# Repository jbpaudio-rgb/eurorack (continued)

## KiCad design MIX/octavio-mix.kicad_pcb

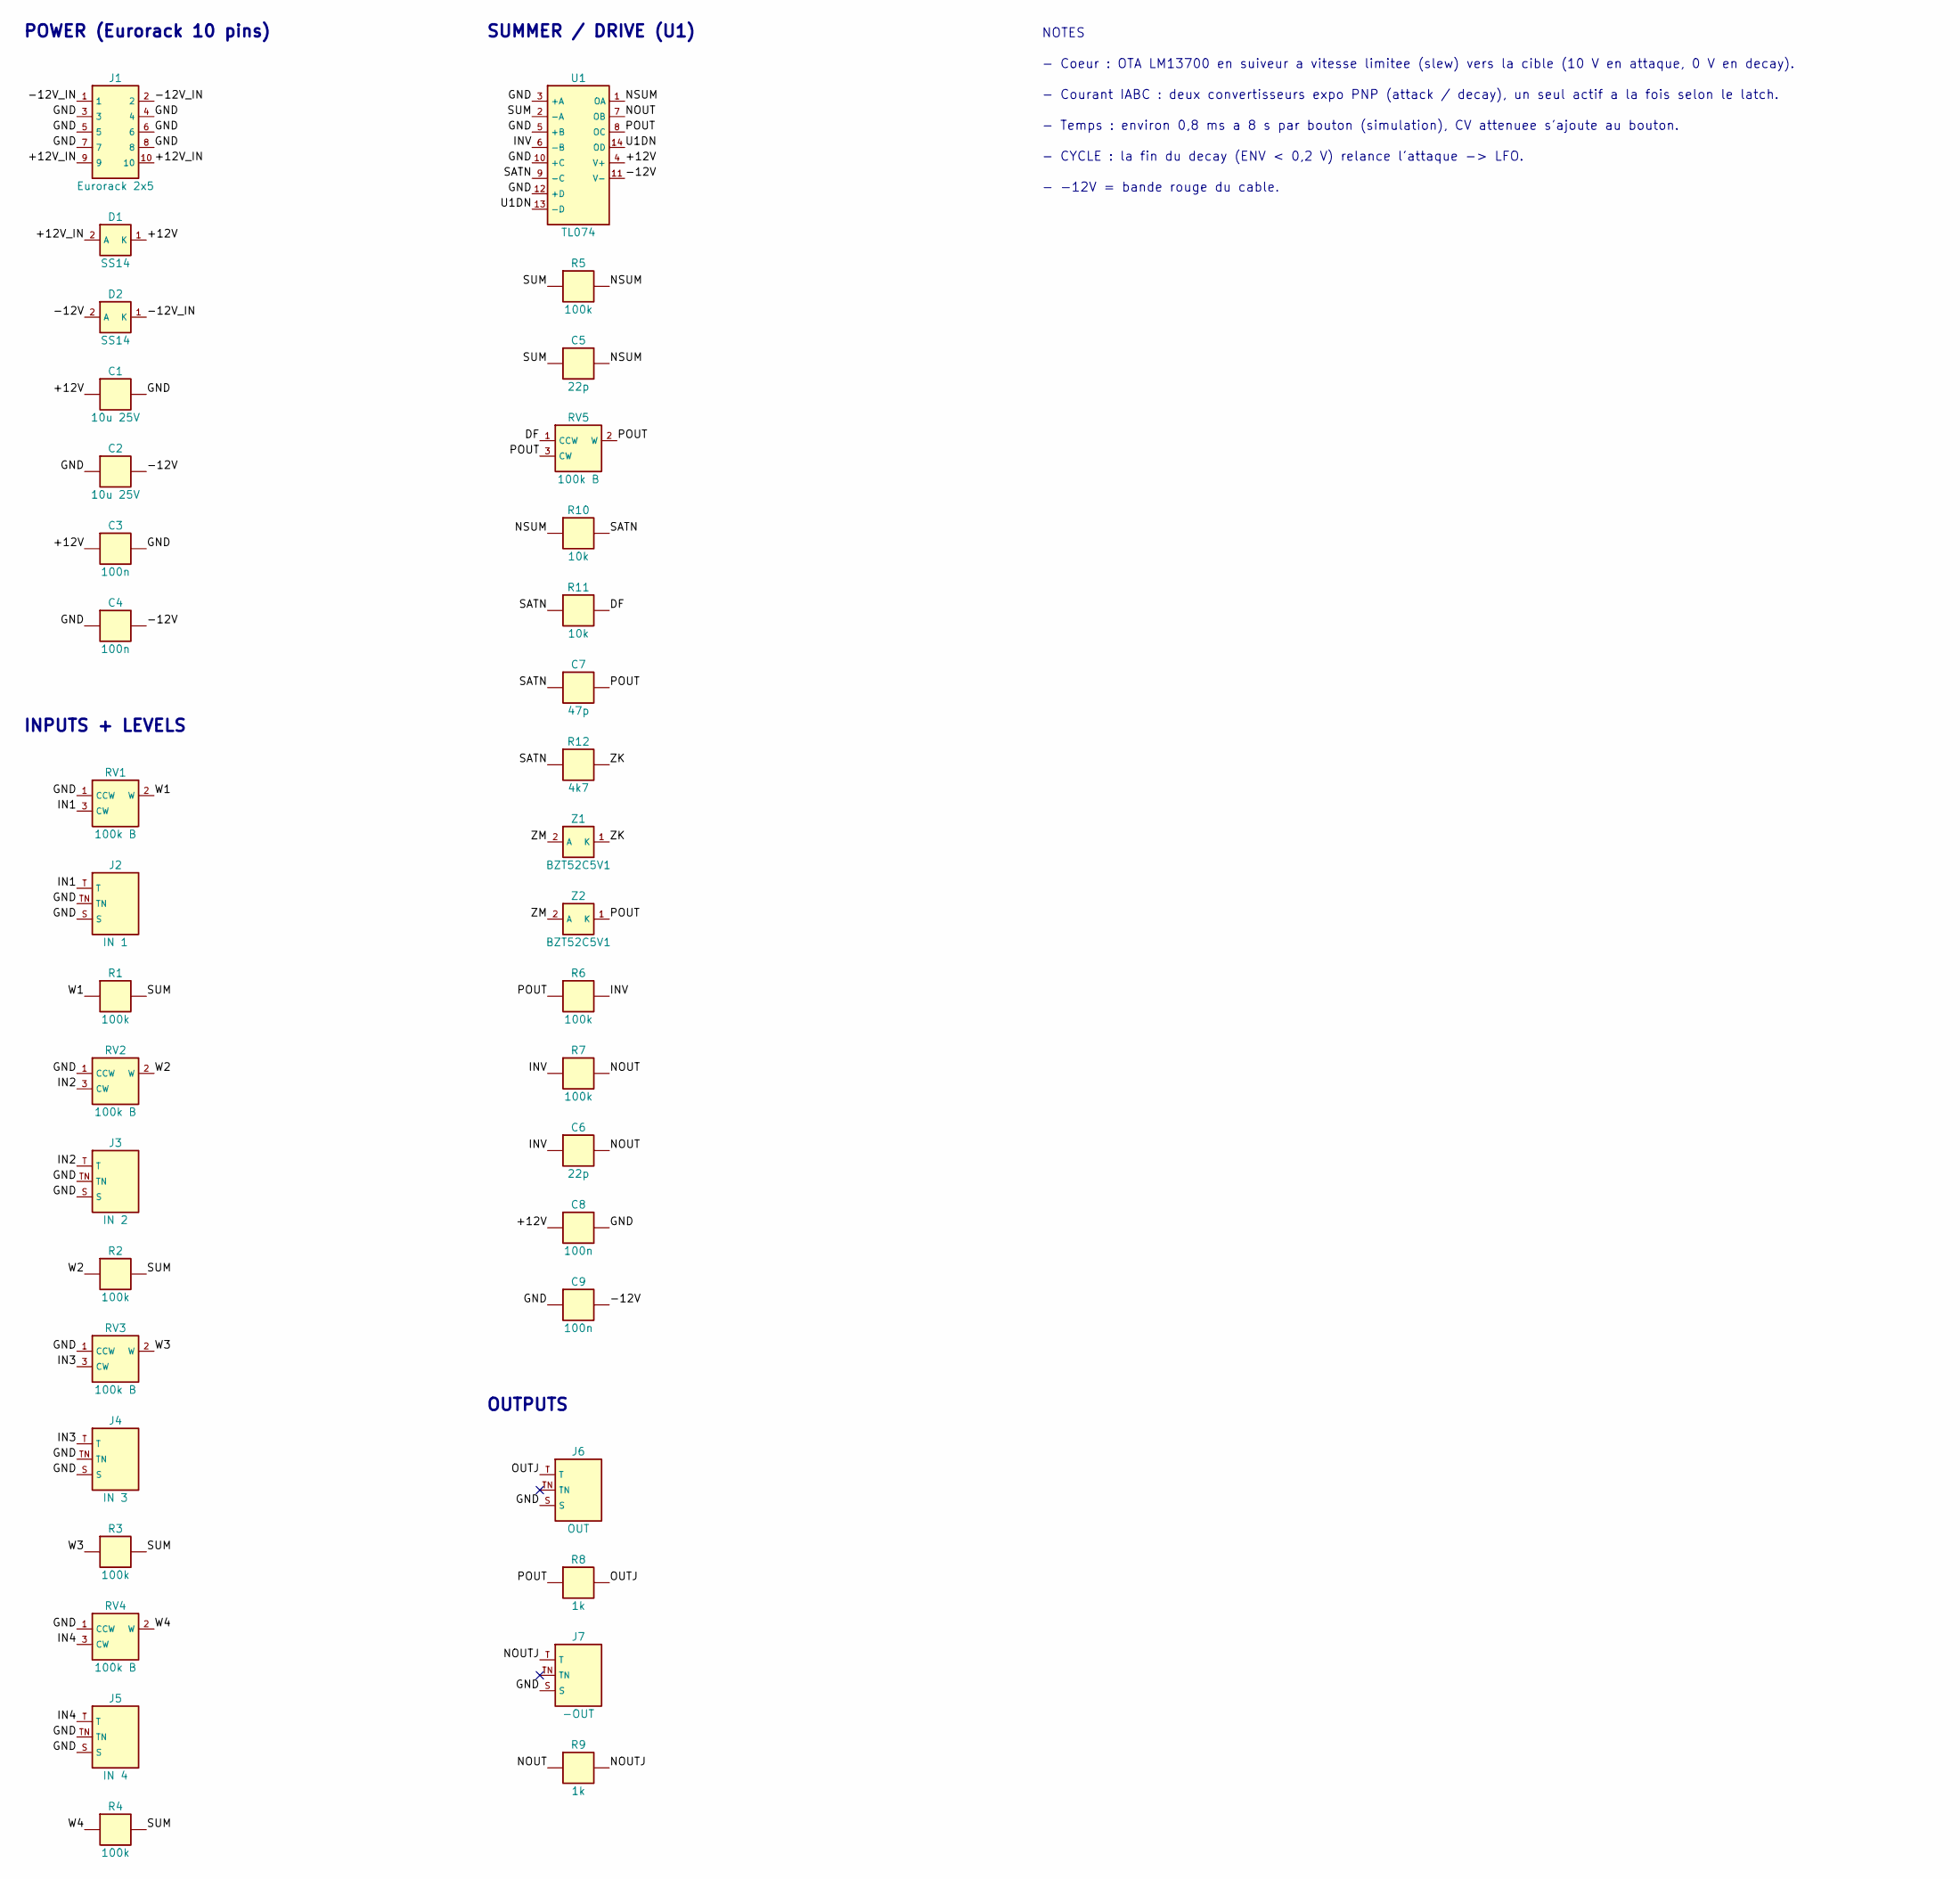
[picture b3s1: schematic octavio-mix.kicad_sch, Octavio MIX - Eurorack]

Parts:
C1, C2: 10u 25V; C_1206_3216Metric; MPN X5R/X7R 1206
C3, C4, C8, C9: 100n; C_0805_2012Metric
C5, C6: 22p; C_0805_2012Metric
C7: 47p; C_0805_2012Metric
D1, D2: SS14; D_SMA; MPN SS14 (40 V 1 A Schottky)
J1: Eurorack 2x5; IDC-Header_2x05_P2.54mm_Vertical; MPN Shrouded header 2x5 2.54 mm
J2: IN 1; Jack_3.5mm_Thonkiconn_PJ398SM; MPN QingPu WQP-PJ301M-12 (Thonkiconn)
J3: IN 2; Jack_3.5mm_Thonkiconn_PJ398SM; MPN QingPu WQP-PJ301M-12 (Thonkiconn)
J4: IN 3; Jack_3.5mm_Thonkiconn_PJ398SM; MPN QingPu WQP-PJ301M-12 (Thonkiconn)
J5: IN 4; Jack_3.5mm_Thonkiconn_PJ398SM; MPN QingPu WQP-PJ301M-12 (Thonkiconn)
J6: OUT; Jack_3.5mm_Thonkiconn_PJ398SM; MPN QingPu WQP-PJ301M-12 (Thonkiconn)
J7: -OUT; Jack_3.5mm_Thonkiconn_PJ398SM; MPN QingPu WQP-PJ301M-12 (Thonkiconn)
R1, R2, R3, R4, R5, R6, R7: 100k; R_0805_2012Metric
R8, R9: 1k; R_0805_2012Metric
R10, R11: 10k; R_0805_2012Metric
R12: 4k7; R_0805_2012Metric
RV1, RV2, RV3, RV4, RV5: 100k B; Pot_Alpha_9mm_Vertical; MPN POT-R09V-100K (9 mm vertical, B100k)
U1: TL074; SOIC-14_3.9x8.7mm_P1.27mm; MPN TL074CDR
Z1, Z2: BZT52C5V1; D_SOD-123; MPN BZT52C5V1 (zener 5,1 V)

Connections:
+12V: C1.1, C3.1, C8.1, D1.1 (K), U1.4 (V+)
+12V_IN: D1.2 (A), J1.9, J1.10
-12V: C2.2, C4.2, C9.2, D2.2 (A), U1.11 (V-)
-12V_IN: D2.1 (K), J1.1, J1.2
DF: R11.2, RV5.1 (CCW)
GND: C1.2, C2.1, C3.2, C4.1, C8.2, C9.1, J1.3, J1.4, J1.5, J1.6, J1.7, J1.8, J2.S, J2.TN, J3.S, J3.TN, J4.S, J4.TN, J5.S, J5.TN, J6.S, J7.S, RV1.1 (CCW), RV2.1 (CCW), RV3.1 (CCW), RV4.1 (CCW), U1.3 (+A), U1.5 (+B), U1.10 (+C), U1.12 (+D)
IN1: J2.T, RV1.3 (CW)
IN2: J3.T, RV2.3 (CW)
IN3: J4.T, RV3.3 (CW)
IN4: J5.T, RV4.3 (CW)
INV: C6.1, R6.2, R7.1, U1.6 (-B)
NOUT: C6.2, R7.2, R9.1, U1.7 (OB)
NOUTJ: J7.T, R9.2
NSUM: C5.2, R5.2, R10.1, U1.1 (OA)
OUTJ: J6.T, R8.2
POUT: C7.2, R6.1, R8.1, RV5.2 (W), RV5.3 (CW), U1.8 (OC), Z2.1 (K)
SATN: C7.1, R10.2, R11.1, R12.1, U1.9 (-C)
SUM: C5.1, R1.2, R2.2, R3.2, R4.2, R5.1, U1.2 (-A)
U1DN: U1.13 (-D), U1.14 (OD)
W1: R1.1, RV1.2 (W)
W2: R2.1, RV2.2 (W)
W3: R3.1, RV3.2 (W)
W4: R4.1, RV4.2 (W)
ZK: R12.2, Z1.1 (K)
ZM: Z1.2 (A), Z2.2 (A)

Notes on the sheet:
POWER (Eurorack 10 pins)
INPUTS + LEVELS
SUMMER / DRIVE (U1)
OUTPUTS
NOTES
- Coeur : OTA LM13700 en suiveur a vitesse limitee (slew) vers la cible (10 V en attaque, 0 V en decay).
- Courant IABC : deux convertisseurs expo PNP (attack / decay), un seul actif a la fois selon le latch.
- Temps : environ 0,8 ms a 8 s par bouton (simulation), CV attenuee s'ajoute au bouton.
- CYCLE : la fin du decay (ENV < 0,2 V) relance l'attaque -> LFO.
- -12V = bande rouge du cable.

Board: 2 copper layers, 38 parts (27 on the bottom side), 25 nets, no tracks yet.

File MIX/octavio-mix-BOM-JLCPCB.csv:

Comment,Designator,Footprint,LCSC Part #,Notes
10u 25V X5R/X7R 1206,"C1,C2",C_1206_3216Metric,,X5R/X7R 1206 - SMT bottom - laisser JLC choisir (Basic de preference)
100n,"C3,C4,C8,C9",C_0805_2012Metric,,SMT bottom - laisser JLC choisir (Basic de preference)
22p,"C5,C6",C_0805_2012Metric,,SMT bottom - laisser JLC choisir (Basic de preference)
47p,C7,C_0805_2012Metric,,SMT bottom - laisser JLC choisir (Basic de preference)
SS14,"D1,D2",D_SMA,,SS14 (40 V 1 A Schottky) - SMT bottom - laisser JLC choisir (Basic de preference)
Eurorack 2x5,J1,IDC-Header_2x05_P2.54mm_Vertical,,Shrouded header 2x5 2.54 mm - THT (wave soldering) - laisser JLC choisir (Basic de preference)
IN 1,J2,Jack_3.5mm_Thonkiconn_PJ398SM,C9900080080,QingPu WQP-PJ301M-12 (Thonkiconn) - THT (wave soldering)
IN 2,J3,Jack_3.5mm_Thonkiconn_PJ398SM,C9900080080,QingPu WQP-PJ301M-12 (Thonkiconn) - THT (wave soldering)
IN 3,J4,Jack_3.5mm_Thonkiconn_PJ398SM,C9900080080,QingPu WQP-PJ301M-12 (Thonkiconn) - THT (wave soldering)
IN 4,J5,Jack_3.5mm_Thonkiconn_PJ398SM,C9900080080,QingPu WQP-PJ301M-12 (Thonkiconn) - THT (wave soldering)
OUT,J6,Jack_3.5mm_Thonkiconn_PJ398SM,C9900080080,QingPu WQP-PJ301M-12 (Thonkiconn) - THT (wave soldering)
-OUT,J7,Jack_3.5mm_Thonkiconn_PJ398SM,C9900080080,QingPu WQP-PJ301M-12 (Thonkiconn) - THT (wave soldering)
100k 1% 0805,"R1,R2,R3,R4,R5,R6,R7",R_0805_2012Metric,,SMT bottom - laisser JLC choisir (Basic de preference)
10k 1% 0805,"R10,R11",R_0805_2012Metric,,SMT bottom - laisser JLC choisir (Basic de preference)
4k7 1% 0805,R12,R_0805_2012Metric,,SMT bottom - laisser JLC choisir (Basic de preference)
1k 1% 0805,"R8,R9",R_0805_2012Metric,,SMT bottom - laisser JLC choisir (Basic de preference)
100k B,"RV1,RV2,RV3,RV4,RV5",Pot_Alpha_9mm_Vertical,C9900018037,"POT-R09V-100K (9 mm vertical, B100k) - THT (wave soldering)"
TL074CDR,U1,SOIC-14_3.9x8.7mm_P1.27mm,C12594,TL074CDR - SMT bottom
BZT52C5V1,"Z1,Z2",D_SOD-123,,"BZT52C5V1 (zener 5,1 V) - SMT bottom - laisser JLC choisir (Basic de preference)"
